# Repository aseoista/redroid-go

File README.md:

> [!WARNING]
> In every commit and release before [0a4a438](https://github.com/aseoista/redroid-go/commit/0a4a438) (including **v1.0.2**), transistor **Q2** was connected in reverse. You should **build the device from the _master_ branch**, where this is fixed, until a new release is issued.

REDROID-GO is an open-source, custom-designed handheld gaming console inspired by the original ODROID-GO. This project enhances the original (discontinued) design with modern features, while maintaining as much as possible software compatibility.

|  |  |  |
| :---: | :---: | :---: |
| Full Build | PCB Front  | PCB Back | 

## Features
- **USB-C Connector** – Modern power and data connectivity.
- **Optional IPS Display** – Upgrade to a vibrant IPS screen instead of the standard TFT.
- **High Software Compatibility** – Works with ODROID-GO software, but unfortunately some patches may be required, see below.
- **Fully Open-Source** ❤️ – Schematics, PCB, and BOM included!

## Repository Contents
- **KiCad Project** – Includes schematic, PCB design, and layout.
- **FreeCAD Project** – Design of the shell.
- **Bill of Materials (BOM)** – All of the PCB components are sourced from LCSC. Other components, such as the display, speaker, battery, buttons need to be bought separately.

### Branching Structure
The _master_ branch contains the latest, **unstable** version of the project, which has not been manufactured or tested yet. If you are looking for a stable and tested version, please refer to the **releases** section, where you can find previous working versions of REDROID-GO.

## Compatibility
The base idea is to keep the project as much software-compatible as possible to the original ODROID-GO. There are some caveats though:
- New ESP32-WROVERs require the setting `CONFIG_INT_WDT` set to `y` in ESP-IDF.
- When using the IPS display, the commands to initialize it should include an additional `0x21`. This is because even if the IPS display uses the same driver IC as the TFT one, by default the colors are inverted.

## Hardware Fabrication
For a full guide to build the device, refer to [BUILDING.md](BUILDING.md)!
### Ordering the PCB
You can order the PCB directly from the `gerber.zip` release artifact using any common PCB manufacturer.<br>
Specs for ordering:
- **Thickness:** 1.6 mm, **required** to make it fit in the case
- **Finish:** ENIG is **strongly recommended**. ENIG provides a flatter and more durable pad surface than HASL, which ensures more consistent readings from the membrane buttons over time.

### Soldering the Components
All components can be soldered by hand.

**Tips**
- A regular soldering iron is sufficient — use a **thin tip** for finer control
- Apply **no-clean flux or thermal flux** to ease solder flow and avoid bridges
- **Start with the USB-C connector and the display connector** — they are the most difficult parts to solder; then proceed with the remaining components
- A **desoldering braid** can be very useful to wick away any excess solder or to correct bridges
- When done soldering, clean the PCB with **isopropyl alcohol (≥90% IPA)**, especially around the buttons’ pads, using a brush or lint-free wipe; let it dry fully before powering

### Shell
The shell can be 3D printed using the STL files contained in the `case.zip` release artifact.

## Software
This device can be programmed like any other ESP32-based board.<br>
A customized bootloader is available in this [fork](https://github.com/aseoista/odroid-go-multi-firmware) of the original [odroid-go-multi-firmware](https://github.com/ducalex/odroid-go-multi-firmware).  
For emulation, the recommended firmware is this [fork](https://github.com/aseoista/retro-go) of [retro-go](https://github.com/ducalex/retro-go).

## Contributing
Contributions are welcome! Feel free to submit pull requests or open issues to discuss improvements.

## Acknowledgments
Special thanks to **Hardkernel** for the original ODROID-GO design and the open-source community for keeping retro gaming alive. Thanks also to:
 -  [32teeth](https://github.com/32teeth) for the membrane buttons library.
 -  [DoganM95](https://github.com/DoganM95) and [snakeye](https://github.com/snakeye) for references on USB PD resistors and auto programming of the ESP32 (see [CH340C-Serial-Programmer](https://github.com/DoganM95/CH340C-Serial-Programmer) and [ch340g-esp32](https://github.com/snakeye/ch340g-esp32)).
 -  [ducalex](https://github.com/ducalex) for providing awesome software for the platform such as _odroid-go-multi-firmware_ and _retro-go_.

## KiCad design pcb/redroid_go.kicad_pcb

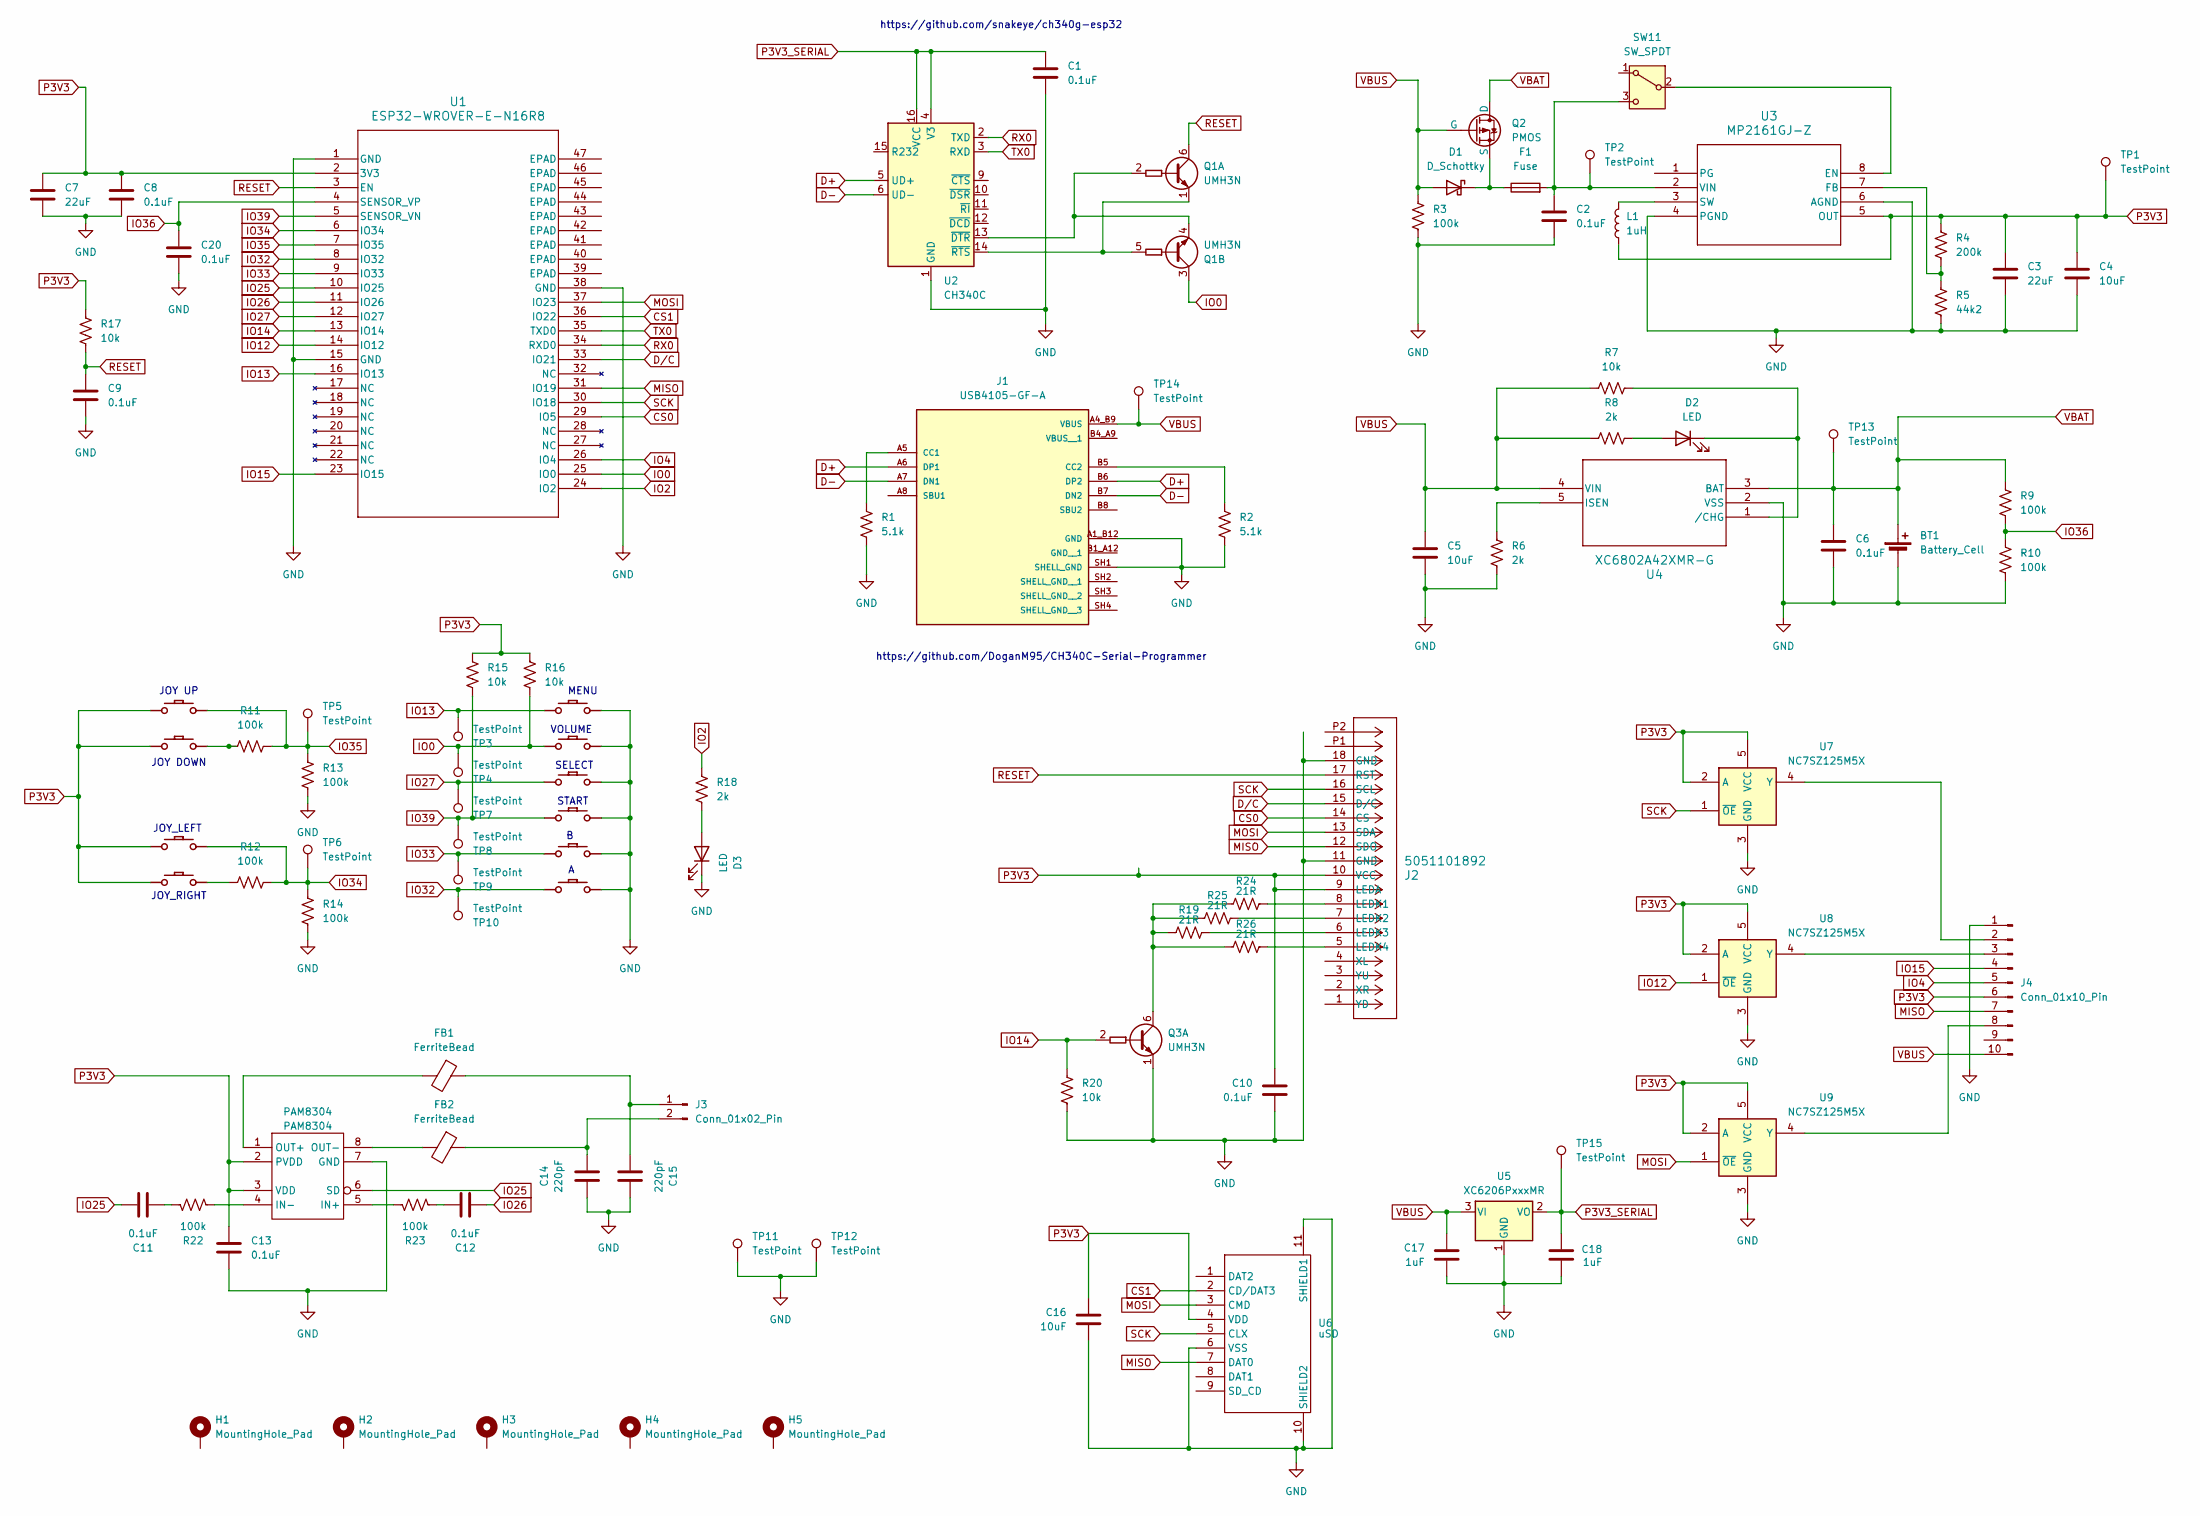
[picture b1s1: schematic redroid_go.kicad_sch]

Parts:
BT1: Battery_Cell; JST_GH_SM02B-GHS-TB_1x02-1MP_P1.25mm_Horizontal
C1, C2, C6, C8, C9, C10, C11, C12, C13, C20: 0.1uF; C_0603_1608Metric_Pad1.08x0.95mm_HandSolder
C3, C7: 22uF; C_0603_1608Metric_Pad1.08x0.95mm_HandSolder
C4, C5, C16: 10uF; C_0603_1608Metric_Pad1.08x0.95mm_HandSolder
C14, C15: 220pF; C_0603_1608Metric_Pad1.08x0.95mm_HandSolder
C17, C18: 1uF; C_0603_1608Metric_Pad1.08x0.95mm_HandSolder
D1: D_Schottky; Nexperia_CFP3_SOD-123W
D2, D3: LED; LED_D3.0mm
F1: Fuse; Fuse_0603_1608Metric
FB1, FB2: FerriteBead; L_0603_1608Metric_Pad1.05x0.95mm_HandSolder
H1, H2, H3, H4, H5: MountingHole_Pad; MountingHole_2.2mm_M2_DIN965_Pad
J1: USB4105-GF-A; GCT_USB4105-GF-A; PARTREV B4
J2: 5051101892; CON_5051101892_MOL
J3: Conn_01x02_Pin; JST_GH_SM02B-GHS-TB_1x02-1MP_P1.25mm_Horizontal
J4: Conn_01x10_Pin; PinSocket_1x10_P2.54mm_Horizontal
L1: 1uH; L_Murata_LQH2MCNxxxx02_2.0x1.6mm
PAM8304: PAM8304; MSOP-8_3x3mm_P0.65mm
Q1, Q3: UMH3N; SOT-363_SC-70-6_Handsoldering
Q2: PMOS; SOT-23
R1, R2: 5.1k; R_0603_1608Metric_Pad0.98x0.95mm_HandSolder
R3, R9, R10, R11, R12, R13, R14, R22, R23: 100k; R_0603_1608Metric_Pad0.98x0.95mm_HandSolder
R4: 200k; R_0603_1608Metric_Pad0.98x0.95mm_HandSolder
R5: 44k2; R_0603_1608Metric_Pad0.98x0.95mm_HandSolder
R6, R8, R18: 2k; R_0603_1608Metric_Pad0.98x0.95mm_HandSolder
R7, R15, R16, R17, R20: 10k; R_0603_1608Metric_Pad0.98x0.95mm_HandSolder
R19, R24, R25, R26: 21R; R_0603_1608Metric_Pad0.98x0.95mm_HandSolder
SW1: UP; CONDUCTIVE_BUTTON_DIRECTIONAL_THICK
SW2: DOWN; CONDUCTIVE_BUTTON_DIRECTIONAL_THICK
SW3: LEFT; CONDUCTIVE_BUTTON_DIRECTIONAL_THICK
SW4: RIGHT; CONDUCTIVE_BUTTON_DIRECTIONAL_THICK
SW5: MENU; CONDUCTIVE_BUTTON_STARTSELECT
SW6: VOLUME; CONDUCTIVE_BUTTON_STARTSELECT
SW7: SELECT; CONDUCTIVE_BUTTON_STARTSELECT
SW8: START; CONDUCTIVE_BUTTON_STARTSELECT
SW9: B; CONDUCTIVE_BUTTON
SW10: A; CONDUCTIVE_BUTTON
SW11: SW_SPDT; MK-12F03-G015
TP1, TP2, TP3, TP4, TP5, TP6, TP7, TP8, TP9, TP10, TP11, TP12, TP13, TP14, TP15: TestPoint; TestPoint_Pad_D1.5mm
U1: ESP32-WROVER-E-N16R8; ESP32-WROVER-E_EXP
U2: CH340C; SOIC-16_3.9x9.9mm_P1.27mm
U3: MP2161GJ-Z; TSOT23-8_MP2161_MNP
U4: XC6802A42XMR-G; SOP_XC6802_TOR
U5: XC6206PxxxMR; SOT-23-3
U6: uSD; SOFNG_TF-15x15
U7, U8, U9: NC7SZ125M5X; SOT-23-5_HandSoldering

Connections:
CS0: J2.14 (CS), U1.29 (IO5)
CS1: U1.36 (IO22), U6.2 (CD/DAT3)
D+: J1.A6 (DP1), J1.B6 (DP2), U2.5 (UD+)
D-: J1.A7 (DN1), J1.B7 (DN2), U2.6 (UD-)
GND: BT1.2 (-), C1.2, C2.2, C3.2, C4.2, C5.2, C6.2, C7.2, C8.2, C9.2, C10.2, C13.2, C14.1, C15.1, C16.2, C17.2, C18.2, C20.2, D3.1 (K), J1.A1_B12 (GND), J1.SH1 (SHELL_GND), J2.11 (GND), J2.18 (GND), J4.1, PAM8304.7 (GND), Q3.1 (E1), R1.2, R2.2, R3.2, R5.2, R6.2, R10.2, R13.1, R14.1, R20.2, SW5.P$GND, SW6.P$GND, SW7.P$GND, SW8.P$GND, SW9.P$GND, SW10.P$GND, TP11.1 (1_1), TP12.1 (1_1), U1.1 (GND), U1.15 (GND), U1.38 (GND), U2.1 (GND), U3.4 (PGND), U3.6 (AGND), U4.2 (VSS), U5.1 (GND), U6.6 (VSS), U6.10 (SHIELD2), U6.11 (SHIELD1), U7.3 (GND), U8.3 (GND), U9.3 (GND)
IO0: Q1.3 (C2), R16.1, SW6.P$ACTIVE, TP4.1 (1_1), U1.25 (IO0)
IO2: R18.2, U1.24 (IO2)
IO4: J4.5, U1.26 (IO4)
IO12: U1.14 (IO12), U8.1 (~OE)
IO13: SW5.P$ACTIVE, TP3.1 (1_1), U1.16 (IO13)
IO14: Q3.2 (B1), R20.1, U1.13 (IO14)
IO15: J4.4, U1.23 (IO15)
IO25: C11.2, PAM8304.6 (SD), U1.10 (IO25)
IO26: C12.1, U1.11 (IO26)
IO27: SW7.P$ACTIVE, TP7.1 (1_1), U1.12 (IO27)
IO32: SW10.P$ACTIVE, TP10.1 (1_1), U1.8 (IO32)
IO33: SW9.P$ACTIVE, TP9.1 (1_1), U1.9 (IO33)
IO34: R12.1, R14.2, SW3.P$GND, TP6.1 (1_1), U1.6 (IO34)
IO35: R11.1, R13.2, SW1.P$GND, TP5.1 (1_1), U1.7 (IO35)
IO36: C20.1, R9.2, R10.1, U1.4 (SENSOR_VP)
IO39: R15.1, SW8.P$ACTIVE, TP8.1 (1_1), U1.5 (SENSOR_VN)
MISO: J2.12 (SDO), J4.7, U1.31 (IO19), U6.7 (DAT0)
MOSI: J2.13 (SDA), U1.37 (IO23), U6.3 (CMD), U9.1 (~OE)
unnamed: C11.1, R22.2
unnamed: C12.2, R23.1
unnamed: D1.1 (K), F1.1, Q2.3 (S)
unnamed: D2.2 (A), R8.2
unnamed: D2.1 (K), R7.2, U4.1 (/CHG)
unnamed: D3.2 (A), R18.1
unnamed: J1.A5 (CC1), R1.1
unnamed: J1.B5 (CC2), R2.1
unnamed: J2.8 (LEDK1), R24.2
unnamed: J2.7 (LEDK2), R25.2
unnamed: J2.6 (LEDK3), R19.2
unnamed: J2.5 (LEDK4), R26.2
unnamed: C15.2, FB1.1, J3.1
unnamed: C14.2, FB2.1, J3.2
unnamed: J4.2, U7.4 (Y)
unnamed: J4.3, U8.4 (Y)
unnamed: J4.8, U9.4 (Y)
unnamed: PAM8304.5 (IN+), R23.2
unnamed: PAM8304.4 (IN-), R22.1
unnamed: FB1.2, PAM8304.1 (OUT+)
unnamed: FB2.2, PAM8304.8 (OUT-)
unnamed: Q1.2 (B1), Q1.4 (E2), U2.13 (~DTR)
unnamed: Q1.1 (E1), Q1.5 (B2), U2.14 (~RTS)
unnamed: Q3.6 (C1), R19.1, R24.1, R25.1, R26.1
unnamed: R11.2, SW2.P$GND
unnamed: R12.2, SW4.P$GND
unnamed: SW11.2 (B), U3.8 (EN)
unnamed: C2.1, F1.2, SW11.3 (C), TP2.1 (1_1), U3.2 (VIN)
unnamed: R4.2, R5.1, U3.7 (FB)
unnamed: L1.1, U3.3 (SW)
unnamed: R6.1, U4.5 (ISEN)
P3V3: C3.1, C4.1, C7.1, C8.1, C10.1, C13.1, C16.1, J2.9 (LEDA), J2.10 (VCC), J4.6, L1.2, PAM8304.2 (PVDD), PAM8304.3 (VDD), R4.1, R15.2, R16.2, R17.1, SW1.P$ACTIVE, SW2.P$ACTIVE, SW3.P$ACTIVE, SW4.P$ACTIVE, TP1.1 (1_1), U1.2 (3V3), U3.5 (OUT), U6.4 (VDD), U7.2 (A), U7.5 (VCC), U8.2 (A), U8.5 (VCC), U9.2 (A), U9.5 (VCC)
P3V3_SERIAL: C1.1, C18.1, TP15.1 (1_1), U2.4 (V3), U2.16 (VCC), U5.2 (VO)
RESET: C9.1, J2.17 (RST), Q1.6 (C1), R17.2, U1.3 (EN)
RX0: U1.34 (RXD0), U2.2 (TXD)
SCK: J2.16 (SCL), U1.30 (IO18), U6.5 (CLX), U7.1 (~OE)
TX0: U1.35 (TXD0), U2.3 (RXD)
VBAT: BT1.1 (+), C6.1, Q2.1 (D), R9.1, TP13.1 (1_1), U4.3 (BAT)
VBUS: C5.1, C17.1, D1.2 (A), J1.A4_B9 (VBUS), J4.10, Q2.2 (G), R3.1, R7.1, R8.1, TP14.1 (1_1), U4.4 (VIN), U5.3 (VI)

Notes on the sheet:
VOLUME
SELECT
JOY DOWN
https://github.com/snakeye/ch340g-esp32
MENU
JOY_RIGHT
JOY UP
JOY_LEFT
START
https://github.com/DoganM95/CH340C-Serial-Programmer

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
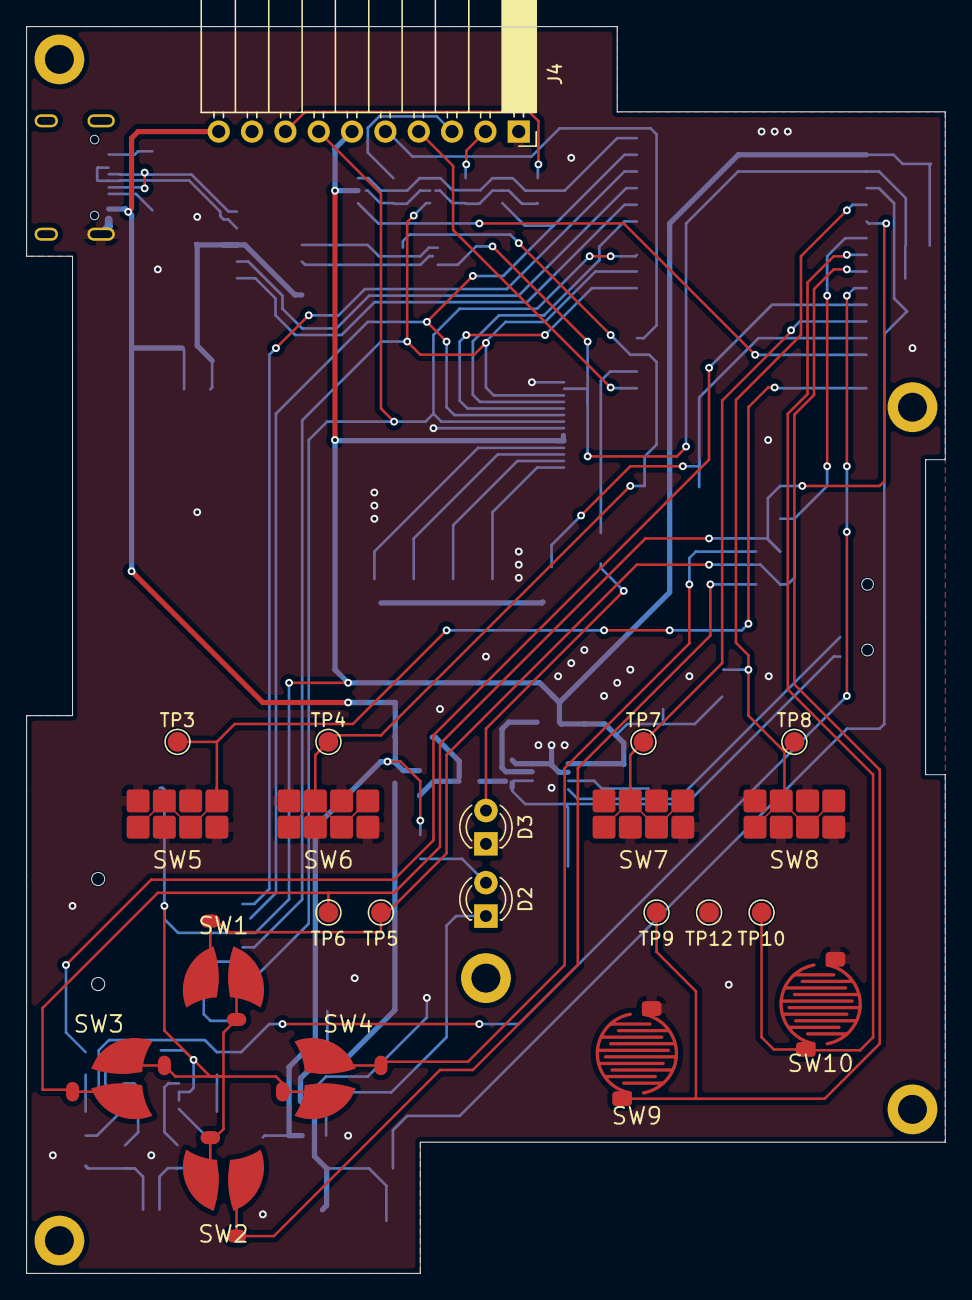
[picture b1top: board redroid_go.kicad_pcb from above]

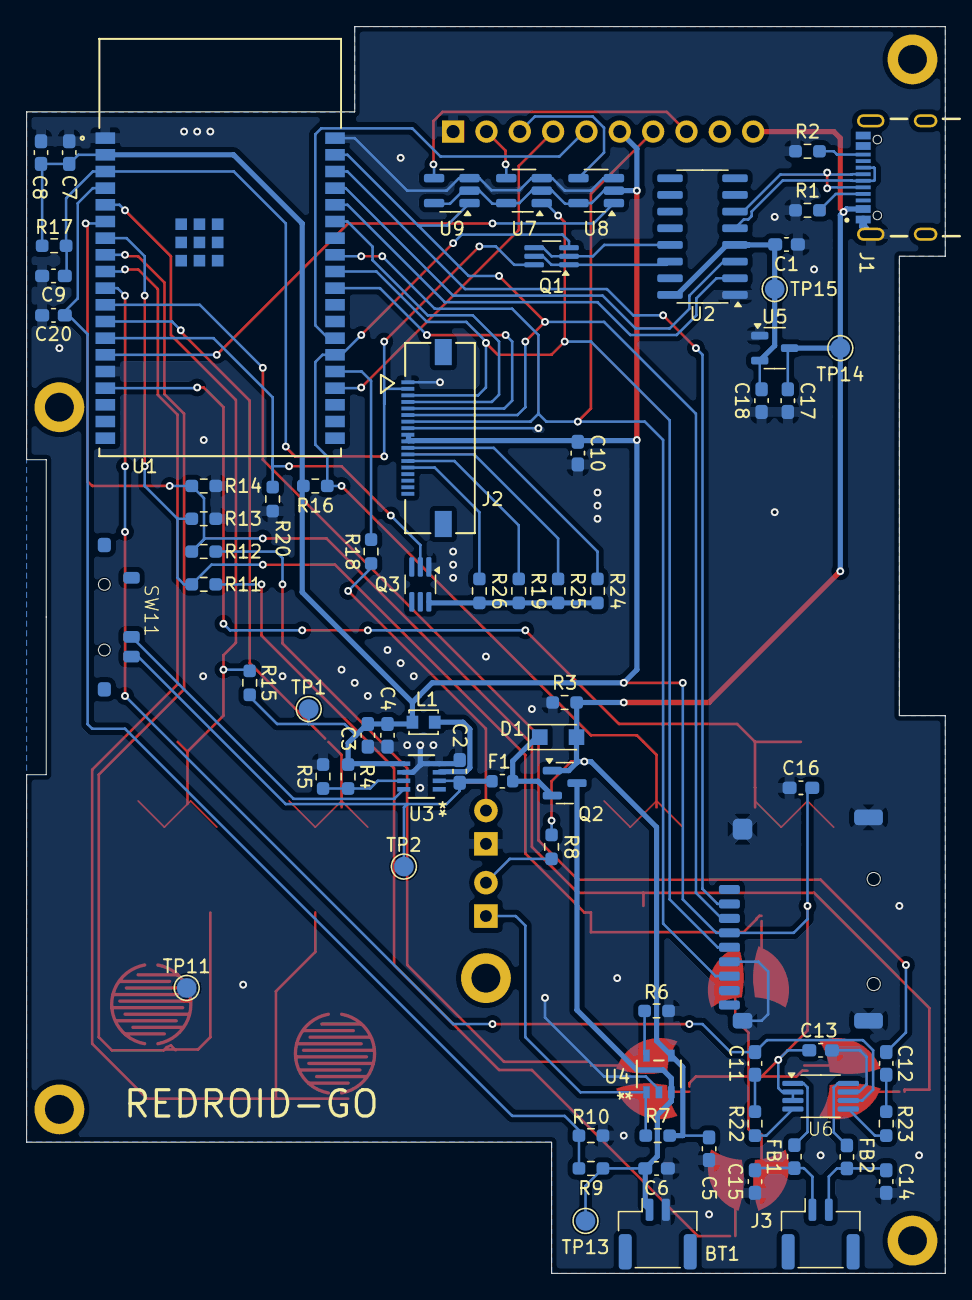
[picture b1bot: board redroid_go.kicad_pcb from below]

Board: 2 copper layers, 70.0 x 95.0 mm, 100 parts (73 on the bottom side), 63 nets.

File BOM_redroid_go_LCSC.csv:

Id,Designator,Footprint,Quantity,Designation,Supplier and ref
1,J4,PinSocket_1x10_P2.54mm_Horizontal,1,Conn_01x10_Pin,C2897392
2,SW2,CONDUCTIVE_BUTTON_DIRECTIONAL_THICK,1,DOWN,
3,SW8,CONDUCTIVE_BUTTON_STARTSELECT,1,START,
4,SW9,CONDUCTIVE_BUTTON,1,B,
5,SW7,CONDUCTIVE_BUTTON_STARTSELECT,1,SELECT,
6,SW1,CONDUCTIVE_BUTTON_DIRECTIONAL_THICK,1,UP,
7,SW3,CONDUCTIVE_BUTTON_DIRECTIONAL_THICK,1,LEFT,
8,"TP9,TP8,TP12,TP5,TP6,TP7,TP10,TP3,TP4,TP14,TP1,TP11,TP2,TP13",TestPoint_Pad_D1.5mm,14,TestPoint,
9,"D3,D2",LED_D3.0mm,2,LED,
10,SW4,CONDUCTIVE_BUTTON_DIRECTIONAL_THICK,1,RIGHT,
11,SW5,CONDUCTIVE_BUTTON_STARTSELECT,1,MENU,
12,SW10,CONDUCTIVE_BUTTON,1,A,
13,SW6,CONDUCTIVE_BUTTON_STARTSELECT,1,VOLUME,
14,"C20,C1,C11,C9,C14,C8,C10,C6,C12,C2",C_0603_1608Metric_Pad1.08x0.95mm_HandSolder,9,0.1uF,C14663
15,"R10,R9,R23,R3,R22,R11,R12,R13,R14",R_0603_1608Metric_Pad0.98x0.95mm_HandSolder,9,100k,C14675
16,"C3,C7",C_0603_1608Metric_Pad1.08x0.95mm_HandSolder,3,22uF,C159801
17,"FB2,FB1",L_0603_1608Metric_Pad1.05x0.95mm_HandSolder,2,FerriteBead,C19330
18,D1,Nexperia_CFP3_SOD-123W,1,D_Schottky,C42441798
19,"R15,R17,R20,R16,R7",R_0603_1608Metric_Pad0.98x0.95mm_HandSolder,5,10k,C98220
20,U3,TSOT23-8_MP2161_MNP,1,MP2161GJ-Z,C3003189
21,U4,SOP_XC6802_TOR,1,XC6802A42XMR-G,C160463
22,"R2,R1",R_0603_1608Metric_Pad0.98x0.95mm_HandSolder,2,5.1k,C881139
23,BT1,JST_GH_SM02B-GHS-TB_1x02-1MP_P1.25mm_Horizontal,1,Battery_Cell,C3029359
24,J1,GCT_USB4105-GF-A,1,USB4105-GF-A,C136423
25,SW11,MK-12F03-G015,1,SW_SPDT,C963208
26,"R25,R19,R24,R26",R_0603_1608Metric_Pad0.98x0.95mm_HandSolder,4,21R,C403071
27,PAM8304,MSOP-8_3x3mm_P0.65mm,1,~,C581342
28,L1,L_Coilcraft_LPS3010,1,1uH,C598616
29,U2,SOIC-16_3.9x9.9mm_P1.27mm,1,CH340C,C84681
30,U6,SOFNG_TF-15x15,1,~,C111196
31,"R8,R6,R18",R_0603_1608Metric_Pad0.98x0.95mm_HandSolder,3,2k,C2907137
32,"U9,U8,U7",SOT-23-5_HandSoldering,3,NC7SZ125M5X,C7420
33,"Q1,Q3",SOT-363_SC-70-6_Handsoldering,2,UMH3N,C62892
34,U1,ESP32-WROVER-E_EXP,1,ESP32-WROVER-E-N16R8,C529589
35,F1,Fuse_0603_1608Metric,1,Fuse,C41380232
36,Q2,SOT-23,1,PMOS,C7422949
37,"C16,C4,C5",C_0603_1608Metric_Pad1.08x0.95mm_HandSolder,4,10uF,C19702
38,R4,R_0603_1608Metric_Pad0.98x0.95mm_HandSolder,1,200k,C49965
39,R5,R_0603_1608Metric_Pad0.98x0.95mm_HandSolder,1,44k2,C2930103
40,J3,JST_GH_SM02B-GHS-TB_1x02-1MP_P1.25mm_Horizontal,1,Conn_01x02_Pin,C3029359
41,J2,CON_5051101892_MOL,1,5051101892,C3249996
42,U10,SOT-23-3,1,GR GR6206P332MR-G,C19631737
43,"C15,C14",C_0603_1608Metric_Pad1.08x0.95mm_HandSolder,2,220pF,C107081
44,U5,Package_TO_SOT_SMD:SOT-23-3,1,XC6206PxxxMR,C5252899
45,"C17,C18",C_0603_1608Metric_Pad1.08x0.95mm_HandSolder,2,1uF,C77044

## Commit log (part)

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2025-01-26 Initial rearrange
2025-01-26 Advances
2025-01-26 Remove files
2025-01-26 Minor changes
2025-01-26 Fixes in silkscreen
2025-01-26 Other fixes in silkscreen
2025-01-26 Other minor fixes
2025-01-26 Fix esp32 label
2025-01-26 Fix via too close to pad
2025-01-26 Minor fixes
2025-01-27 Fix audo amplifier IC name
2025-01-29 Update diode footprint
2025-02-08 Change PCB for step down
2025-02-08 Made power traces more thick
2025-02-08 Minor fix
2025-02-08 Remove duplicated resistor in PCB
2025-02-08 Fixes in labels
2025-02-08 Fix values of some capacitors
2025-02-08 Move labels in PCB
2025-02-08 Change L1 PCB footprint
2025-02-09 Add CI file
2025-02-09 Reduce required vias
2025-02-09 Add BOM for LCSC
2025-02-09 Update CI to use kicad 8
2025-02-09 Fix project name
2025-02-09 Enable workflow_dispatch
2025-02-09 Fix drill command in CI
2025-02-09 Add project name label
2025-02-09 Dynamic versioning of pcb
2025-02-09 Update BOM
2025-02-11 Flip side of LED, fix position of test pad
2025-03-10 Convert to KiCad 9
2025-03-11 Fix battery/VBUS PMOS polarity
2025-03-11 Add separate power for serial chip
2025-03-11 Minor fix in via
2025-03-11 Move SD card connector
2025-03-12 Change 3v3 LDO to AMS1117 and add test point
2025-03-12 Minor fix in PCB labels
2025-03-12 Cleanup tracks and vias
2025-03-14 Remove solder paste in buttons
2025-03-14 Remove paste in menu buttons
2025-03-14 Update menu button footprints
2025-03-14 Fix board display margin
2025-03-14 Fix ISEN resistor in battery charger
2025-03-15 Update kicad to 9.0 in CI
2025-03-15 Add missing via
2025-03-16 Update audio out filter capacitors
2025-03-16 Fix 3V3_SERIAL capacitors
2025-03-16 Minor fixes in PCB
2025-03-16 Remove generated files
2025-03-16 Add datasheet of compatible component
2025-03-16 Update README.md
    Add logo
2025-03-29 Move SD socket
2025-04-13 Move display connector and minor fixes
2025-04-13 Add new mouting hole
2025-04-16 Add acknowlegements to README.md
2025-04-22 Change DPAD resistors
2025-05-10 Rename label
2025-05-10 Fix filled zones
2025-05-10 Move menu buttons
2025-05-10 Change serial LDO to SOT23-3 and update BOM
2025-05-15 Adjust DPAD and menu buttons pad position
2025-05-15 Improve A and B buttons pads
2025-05-26 Relocate components
2025-05-27 Minor fixes in F.Silkscreen
2025-05-27 Move test pads
2025-05-27 Improve charge LED resistor
2025-05-28 Various fixes
2025-05-29 Integrate feedback from JLCDFM
2025-06-01 Update 3v3 trace
2025-06-02 Improve symmetry of audio components
2025-08-13 Move PCB-related files in folder
2025-08-13 Add initial case
2025-08-13 Add STL generation workflow
2025-08-13 Fix STL wf
2025-08-14 Attempt to automatically make release from tag
2025-08-14 Improve LED layout
2025-08-14 Change pcb for improved power switch
2025-08-14 Move charge led
2025-08-14 Change led orientation
2025-08-14 Improvements in vias
2025-08-14 Add missing GND connectio to ESP32
2025-08-14 Add BOM for aliexpress sourced parts
2025-08-17 Fix switch hole size
2025-08-21 Move switch again
2025-08-27 Other fix in switch position
2025-08-27 Change switch connection to improve PCB
2025-08-28 Minor fixes in silkscreen
2025-08-28 Move menu buttons up
2025-08-31 Update case front
2025-10-05 Updata case back to support switch
2025-10-16 Enlarge switch hole
2025-10-16 Enlarge GPIO header hole
2025-10-16 Add missing value for some components
2025-10-16 Update LCSC BOM
2025-10-16 Replace old images with new ones in README
    Updated images for the REDROID-GO project in the README.
2025-10-22 Add hardware fabrication details to README
    Added hardware fabrication section with PCB ordering and soldering tips.
2025-10-22 Add shell 3D printing instructions to README
    Added instructions for 3D printing the shell using STL files.
2025-10-22 Add GNU GPL v3 license
    Added the GNU General Public License version 3 to the project.
2025-10-22 Revise repository contents in README
    Updated README to include FreeCAD project and removed assembly instructions note.
2025-10-22 Rename AliExpress BOM
2025-10-23 Add battery in BOM and fix extension
2025-10-24 Document software programming and firmware options
    Added software programming details and firmware recommendations.
2025-10-24 Revise README images
    Updated image layout in README and add device image.
2025-10-24 Fix link in README.md
2025-12-29 Move dpad down
2025-12-29 Increase width to allow resin prints
2025-12-29 Decrease GPIO header socket height
2026-01-11 Add hardware fabrication guide for REDROID-GO
    Added comprehensive hardware fabrication instructions for building a REDROID-GO, including PCB ordering, component buying, soldering guide, and assembly steps.
2026-01-11 Add link to BUILDING.md in README
    Added a reference to the BUILDING.md guide for device assembly.
2026-01-11 Revise test points summary in BUILDING.md
    Updated expected values and conditions for test points in the documentation.
2026-01-11 Enhance CI to include schematic file generation
    Added steps to generate and upload schematic PDF.
2026-01-11 Fix path for schematic file export in CI workflow
2026-01-11 Update PDF file pattern in CI workflow
2026-01-11 Update PDF path to use wildcard in upload step
2026-01-12 Add image to BUILDING.md for hardware fabrication
    Added an image to the hardware fabrication instructions.
2026-01-12 Update building instructions for clarity and completeness
    Clarified instructions on polarized parts and added a step to connect the display.
2026-01-12 Include estimated build time in BUILDING.md
2026-01-13 Fix AliExpress BOM
2026-01-28 Adjust length of back's screw pads
2026-01-28 Reduced length of back's screw pads
2026-02-01 Add button labels
2026-02-01 Update CI export script
2026-02-15 Minoor improvement in position of A button
2026-02-15 Remove unuseful pocket in case
2026-02-24 Adjust position of USB pocket
2026-02-24 Fix dpad position
2026-02-24 Increase heigth of dpad socket
2026-02-26 Minor improvements in dpad holders
